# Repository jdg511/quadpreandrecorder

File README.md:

# Quad Preamp and Recorder

Compact four-channel ambisonic electret preamp, 192 kHz/24-bit recorder,
real-time binaural monitor, and touchscreen controller.

The hardware is derived from
[jdg511/Quadelectretpre](https://github.com/jdg511/Quadelectretpre) and is
redesigned as a mixed-signal two-layer PCB in a Hammond 1590XX enclosure.

## Project layout

- `hardware/` — KiCad project, fabrication package, design notes, and reviews.
- `tools/` — reproducible schematic, PCB, and fabrication-generation scripts.
- `firmware/` — recorder/DSP interface, pin map, file-naming rules, and
  implementation requirements. Production firmware is not included in Rev A.

## Revision status

The current design is **Rev C** (2026-09-08), routed for the compact
**Hammond 1590XX** (138 x 114 mm board, 145 x 121 x 39 mm enclosure). Rev C
takes the Rev B board and:

- adds a **USB-C** receptacle (J9) on the rear wall — 5 V power from any
  charger, power bank or computer port (TPS61175 boost + ADP7142 low-noise
  LDO make the 9 V analog rail), SD-card file transfer (MTP) and firmware
  updates; the 9 V barrel (J1) stays as an alternative input and moved to the
  rear-left wall;
- mutes the 1/4-inch line out with a signal relay (K1) while a computer is
  attached (ground-loop protection, on-screen warning with override);
- replaces the headphone pot with a **TPA6130A2** I2C-volume headphone amp
  (encoder / touchscreen control) and the pad toggle with a GPIO-driven
  level shifter (pad is a touchscreen control);
- changes the display to the LCDWiki **MSP3526** 3.5-inch IPS module with
  FT6336U **capacitive** touch (the MSP3520 named in Rev B is resistive).
- adds an internal **LiPo battery** (5000 mAh, 6-7 h) with a BQ24074 USB
  charger and a two-button soft-power gesture (hold RECORD + encoder push).

Walls: rear = SD slot + 9 V + USB-C, left = mic RJ45 (Amphenol RJHSE-5380),
right = headphones, front = line out; lid = display, record button, gain
encoder. Rev C3 (2026-09-12) removed the J6/J7 test headers (probe at
component pads or the TP3-TP14 pads), moved to a 4-layer SIG/GND/GND/SIG
stack, and made the mic input switchable from the screen: electret bias
off / 5 V / 9 V (one setting for all four channels) and, with the bias off,
the four RJ45 pairs become true balanced inputs for dynamic microphones
(two-op-amp instrumentation stage, +20.1 dB, SPICE-checked CMRR 58-67 dB
worst case across the audio band). The 9 V analog LDO is an ADP7142
(the TPS7A4701 it replaces had no distributor depth) and every BOM line
was re-checked for stock and price the same day. See
`hardware/reviews/audio-rules-check-revC3-fixes.md`, `hardware/mechanical.md`,
`hardware/connector-pinout.md` and `firmware/docs/REV-C-CONTROL-MODEL.md`.

ERC is clean and DRC (`--all-track-errors --schematic-parity
--severity-error`) reports 0 violations, 0 unconnected pads, 0 parity issues
on the routed board. The Gerbers, drills, BOM, placement CSVs, STEP and PDFs
in `hardware/manufacturing/` are regenerated from it
(`QuadPreRecorder-RevC-PCBWay-handoff.zip`). Rev B outputs are archived in
`hardware/manufacturing/revb-archive/`.

Still a human check before ordering: the physical Hammond 1590XX fit (wall
cutouts, button/shaft reach, the purchased MSP3526 module) — see
`hardware/enclosure-1590XX-desk-study.md` and
`hardware/reviews/rev-c-preorder-review.md`.

This is still new mixed-signal hardware, not a bench-proven production
revision. Read the prototype confirmations in `hardware/requirements.md` and
the order/bring-up notes in `hardware/manufacturing/README.md` before ordering.

## Rebuild

- `tools/route_pcb.ps1` regenerates the schematic/footprints/placement, runs
  Freerouting 1.9.0 (`tools/cache/freerouting19.jar`, single-threaded — the
  2.2.4 jar drops nets from its session export on this board), imports the
  route, adds the GND pours, and checks DRC. Allow ~35-60 minutes.
- `python tools/build_manufacturing.py` regenerates the complete PCBWay handoff
  with KiCad 10's command-line tools.

The checked-in routed board is the release artifact; rerouting is not required
to order it.

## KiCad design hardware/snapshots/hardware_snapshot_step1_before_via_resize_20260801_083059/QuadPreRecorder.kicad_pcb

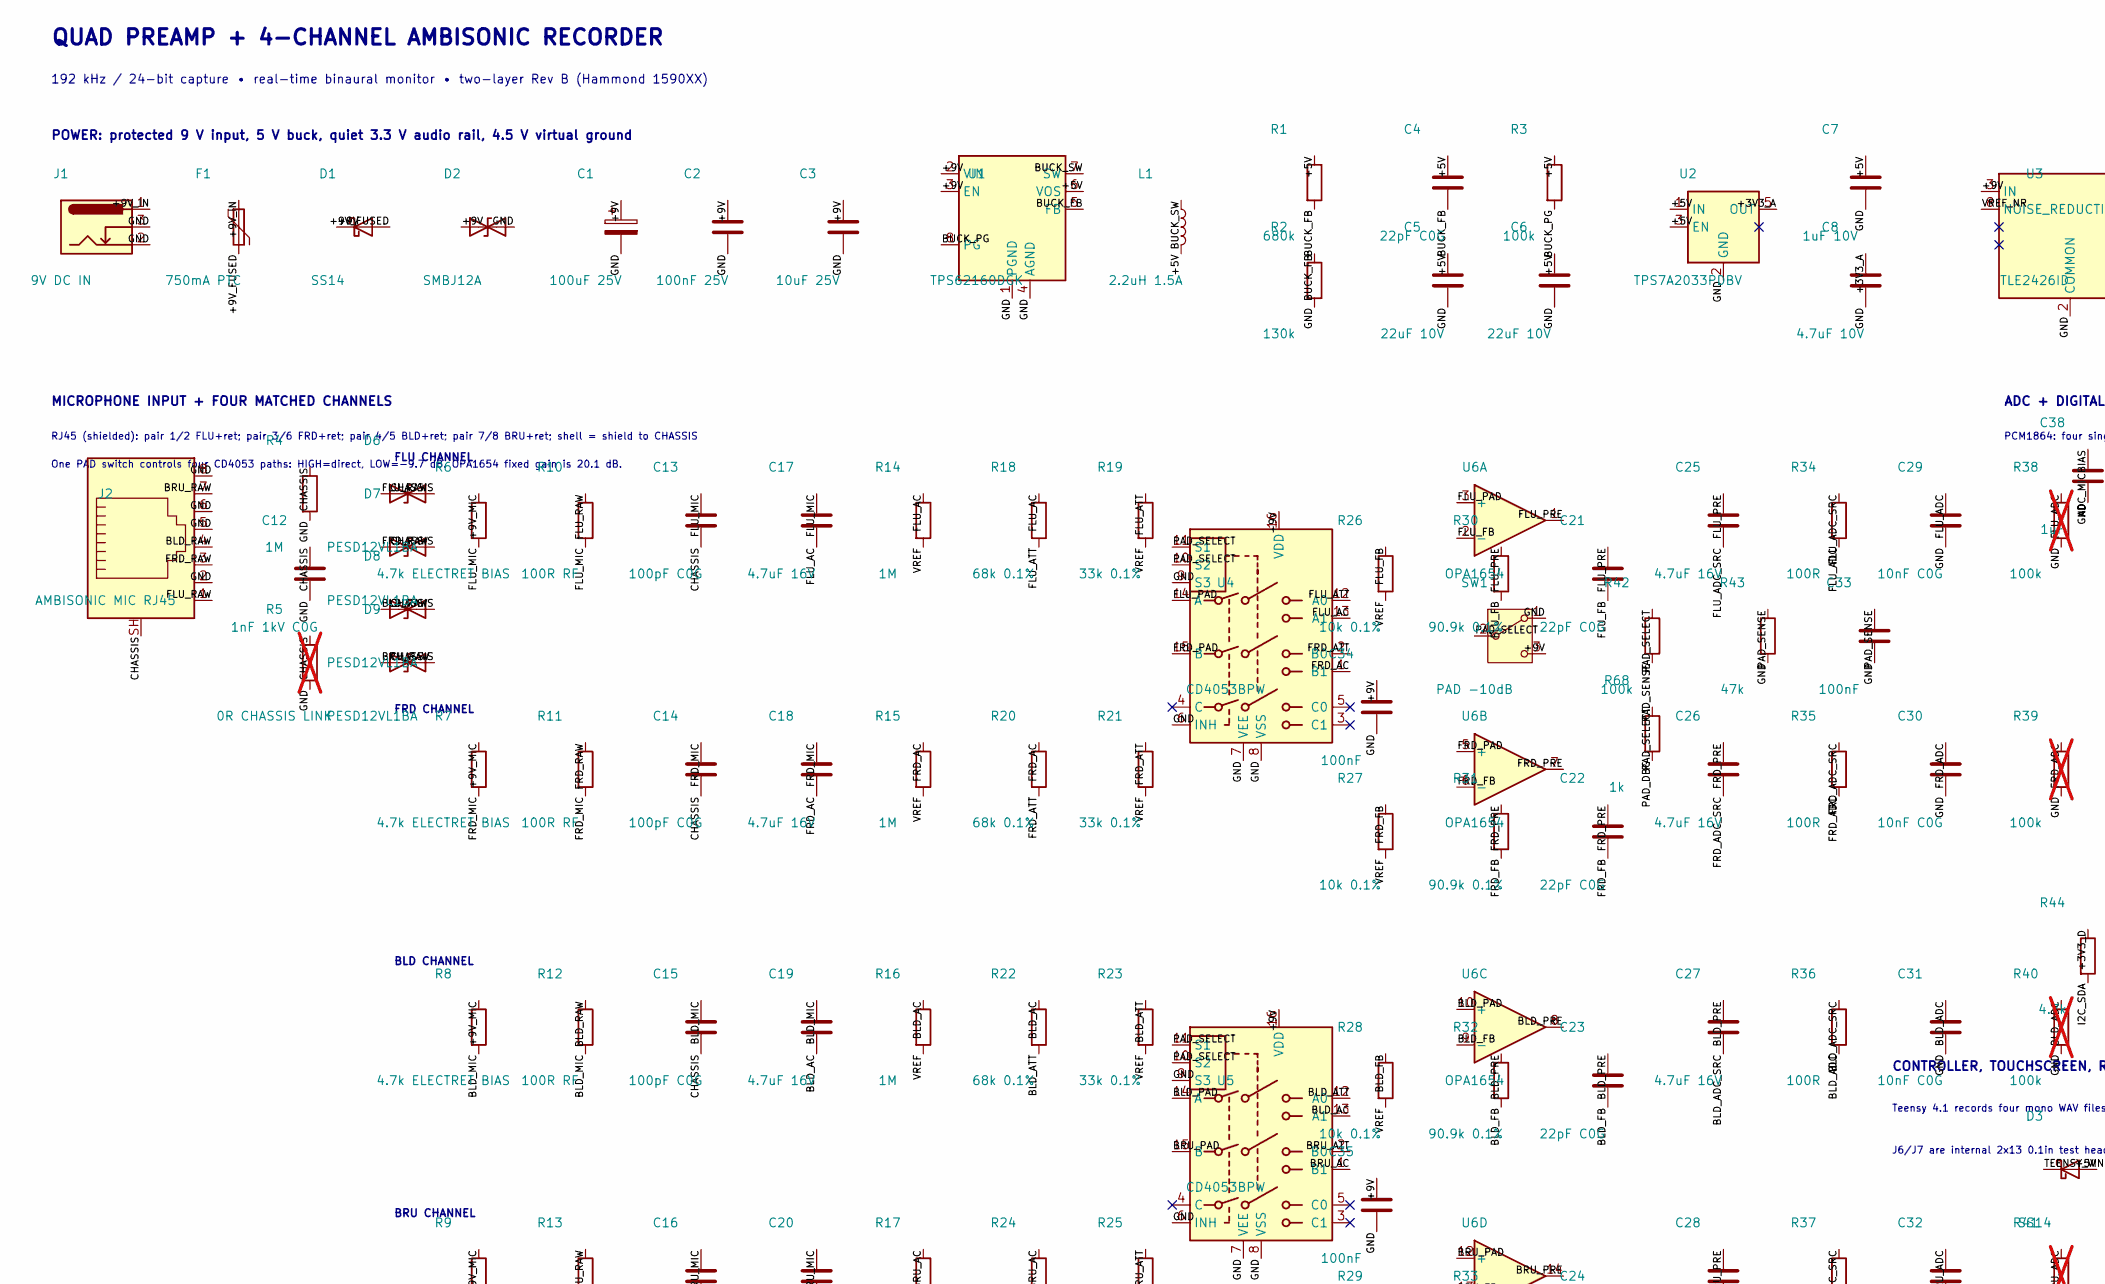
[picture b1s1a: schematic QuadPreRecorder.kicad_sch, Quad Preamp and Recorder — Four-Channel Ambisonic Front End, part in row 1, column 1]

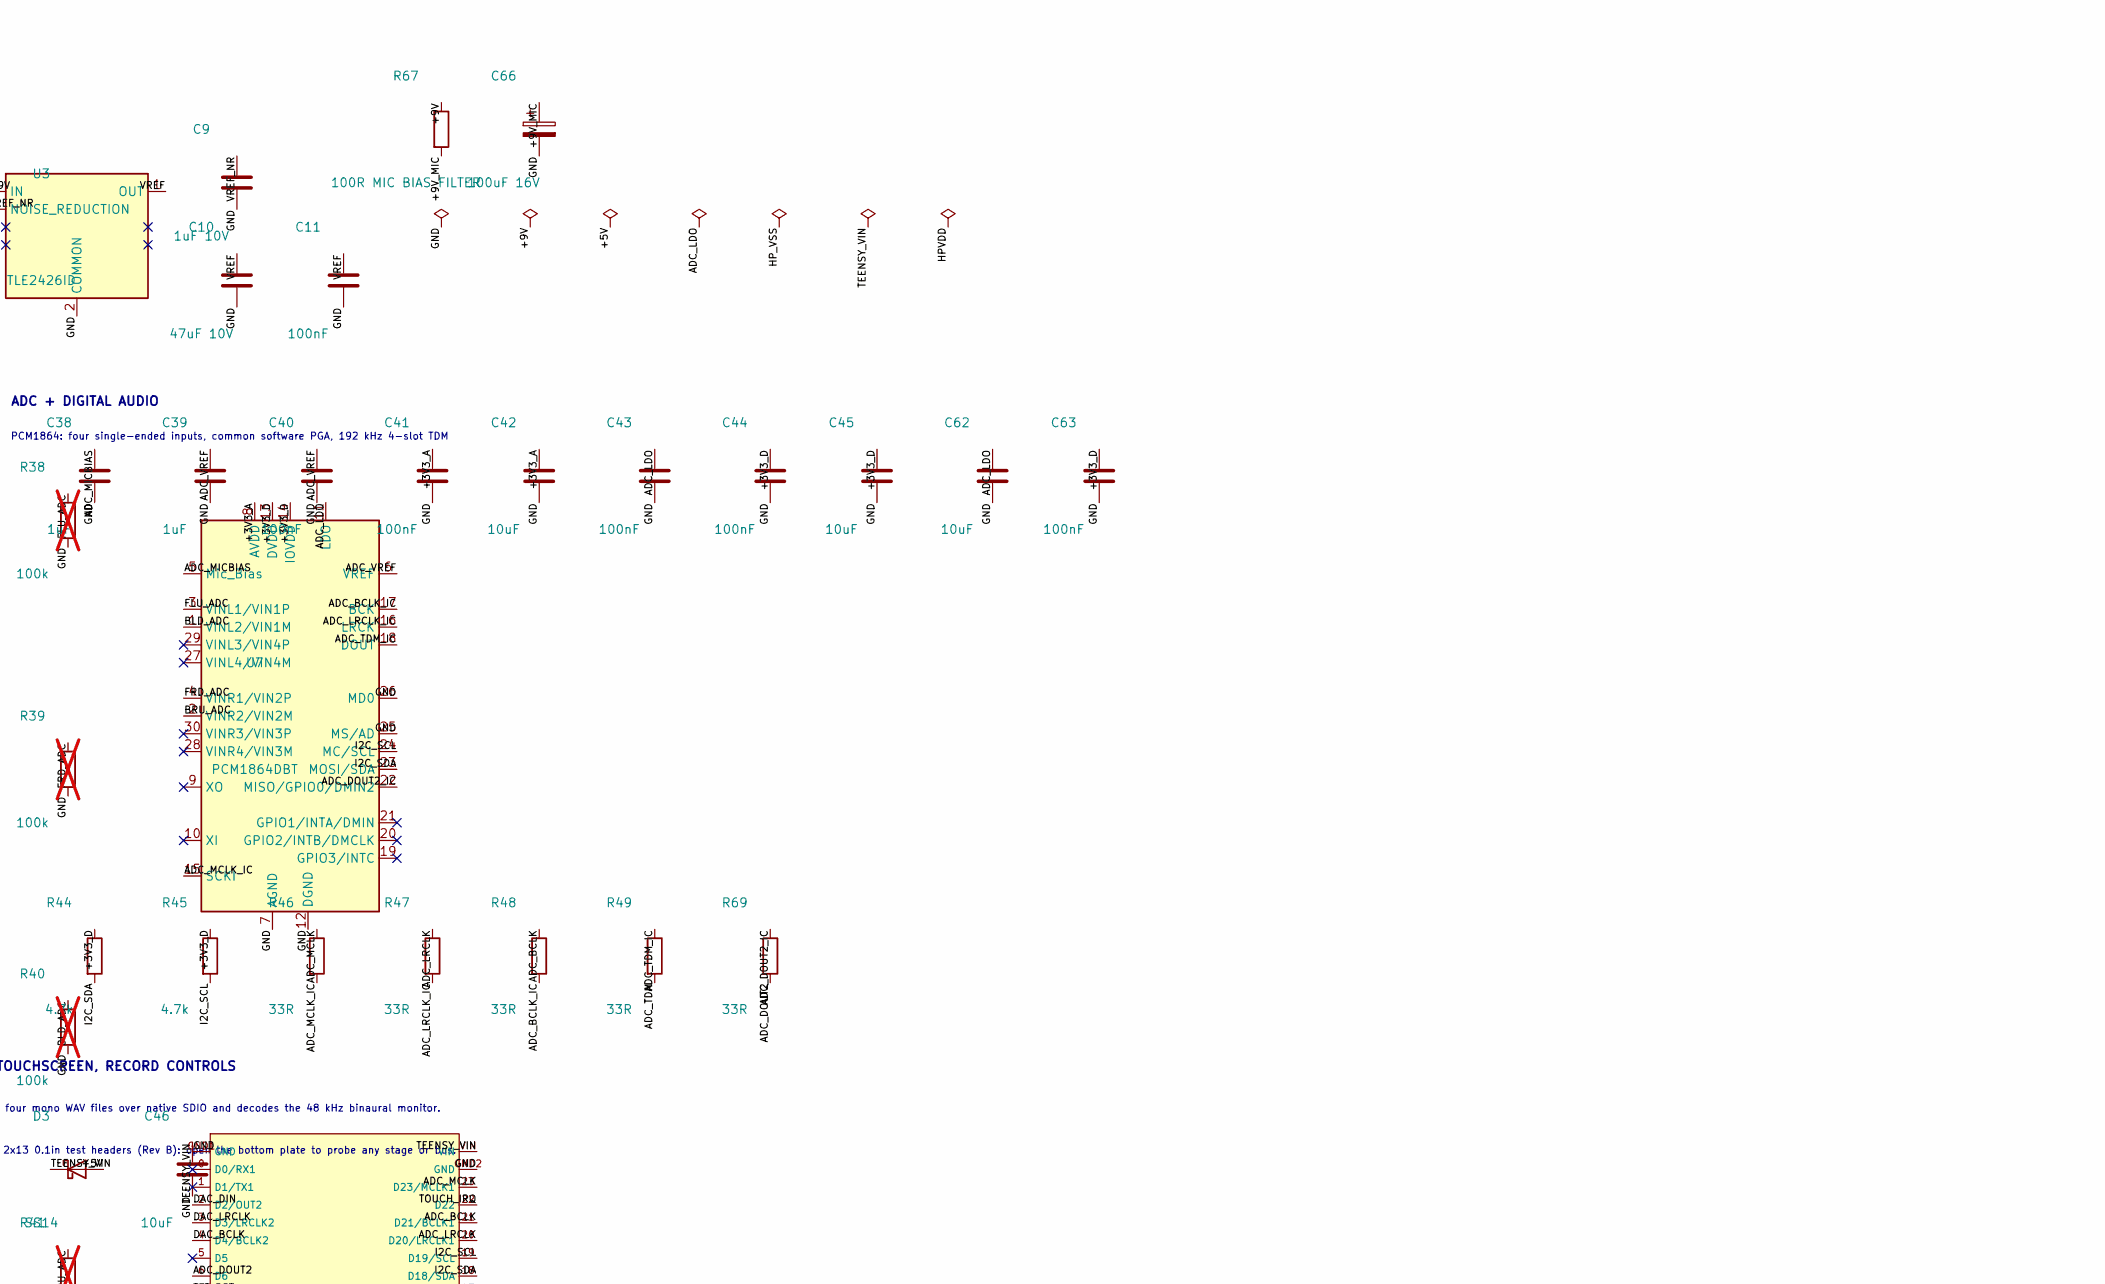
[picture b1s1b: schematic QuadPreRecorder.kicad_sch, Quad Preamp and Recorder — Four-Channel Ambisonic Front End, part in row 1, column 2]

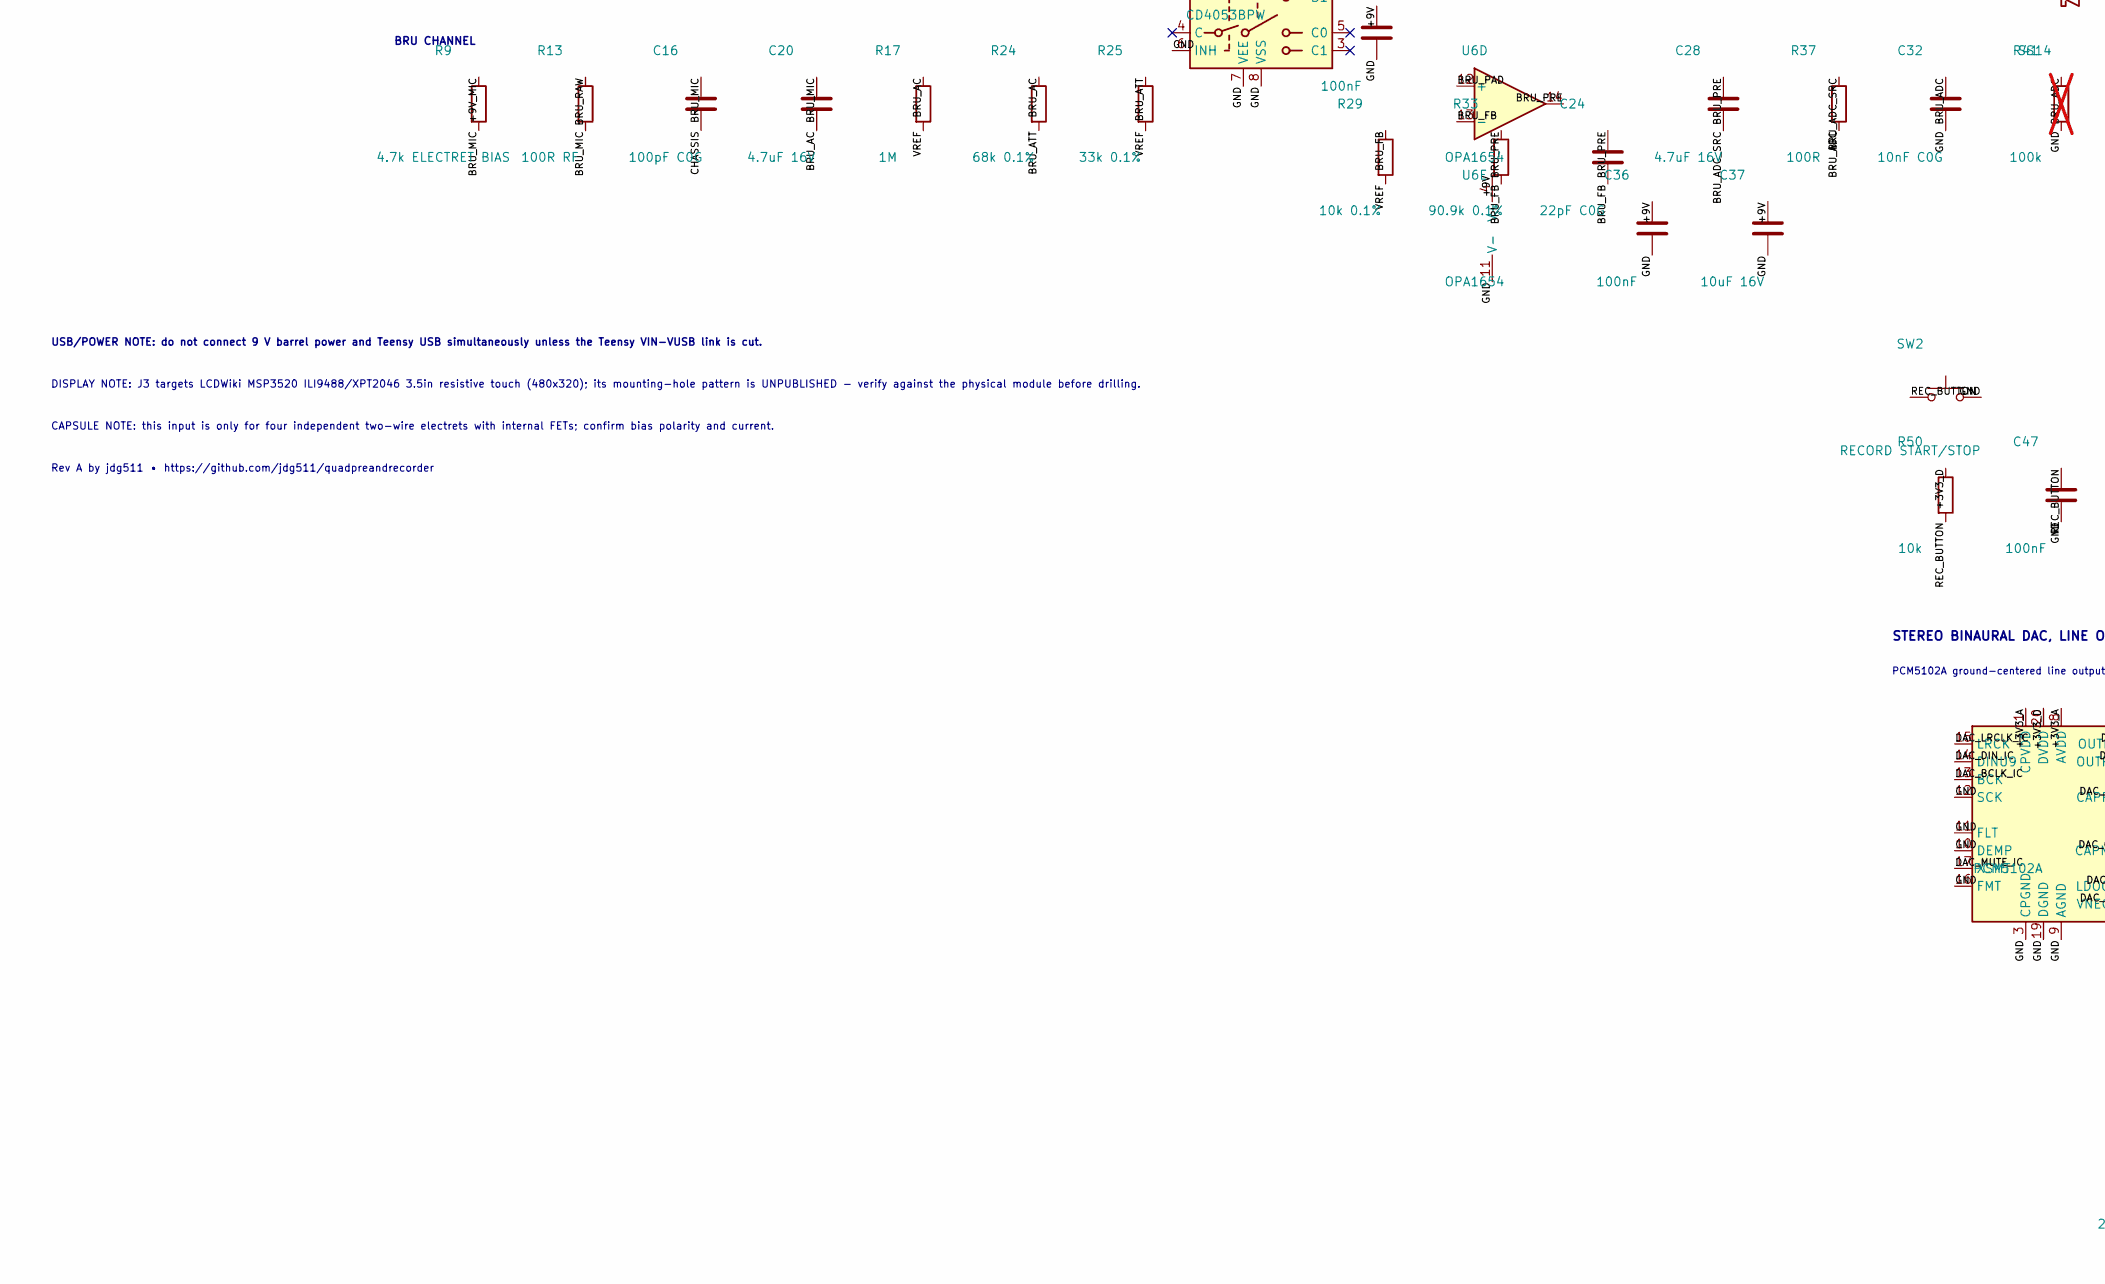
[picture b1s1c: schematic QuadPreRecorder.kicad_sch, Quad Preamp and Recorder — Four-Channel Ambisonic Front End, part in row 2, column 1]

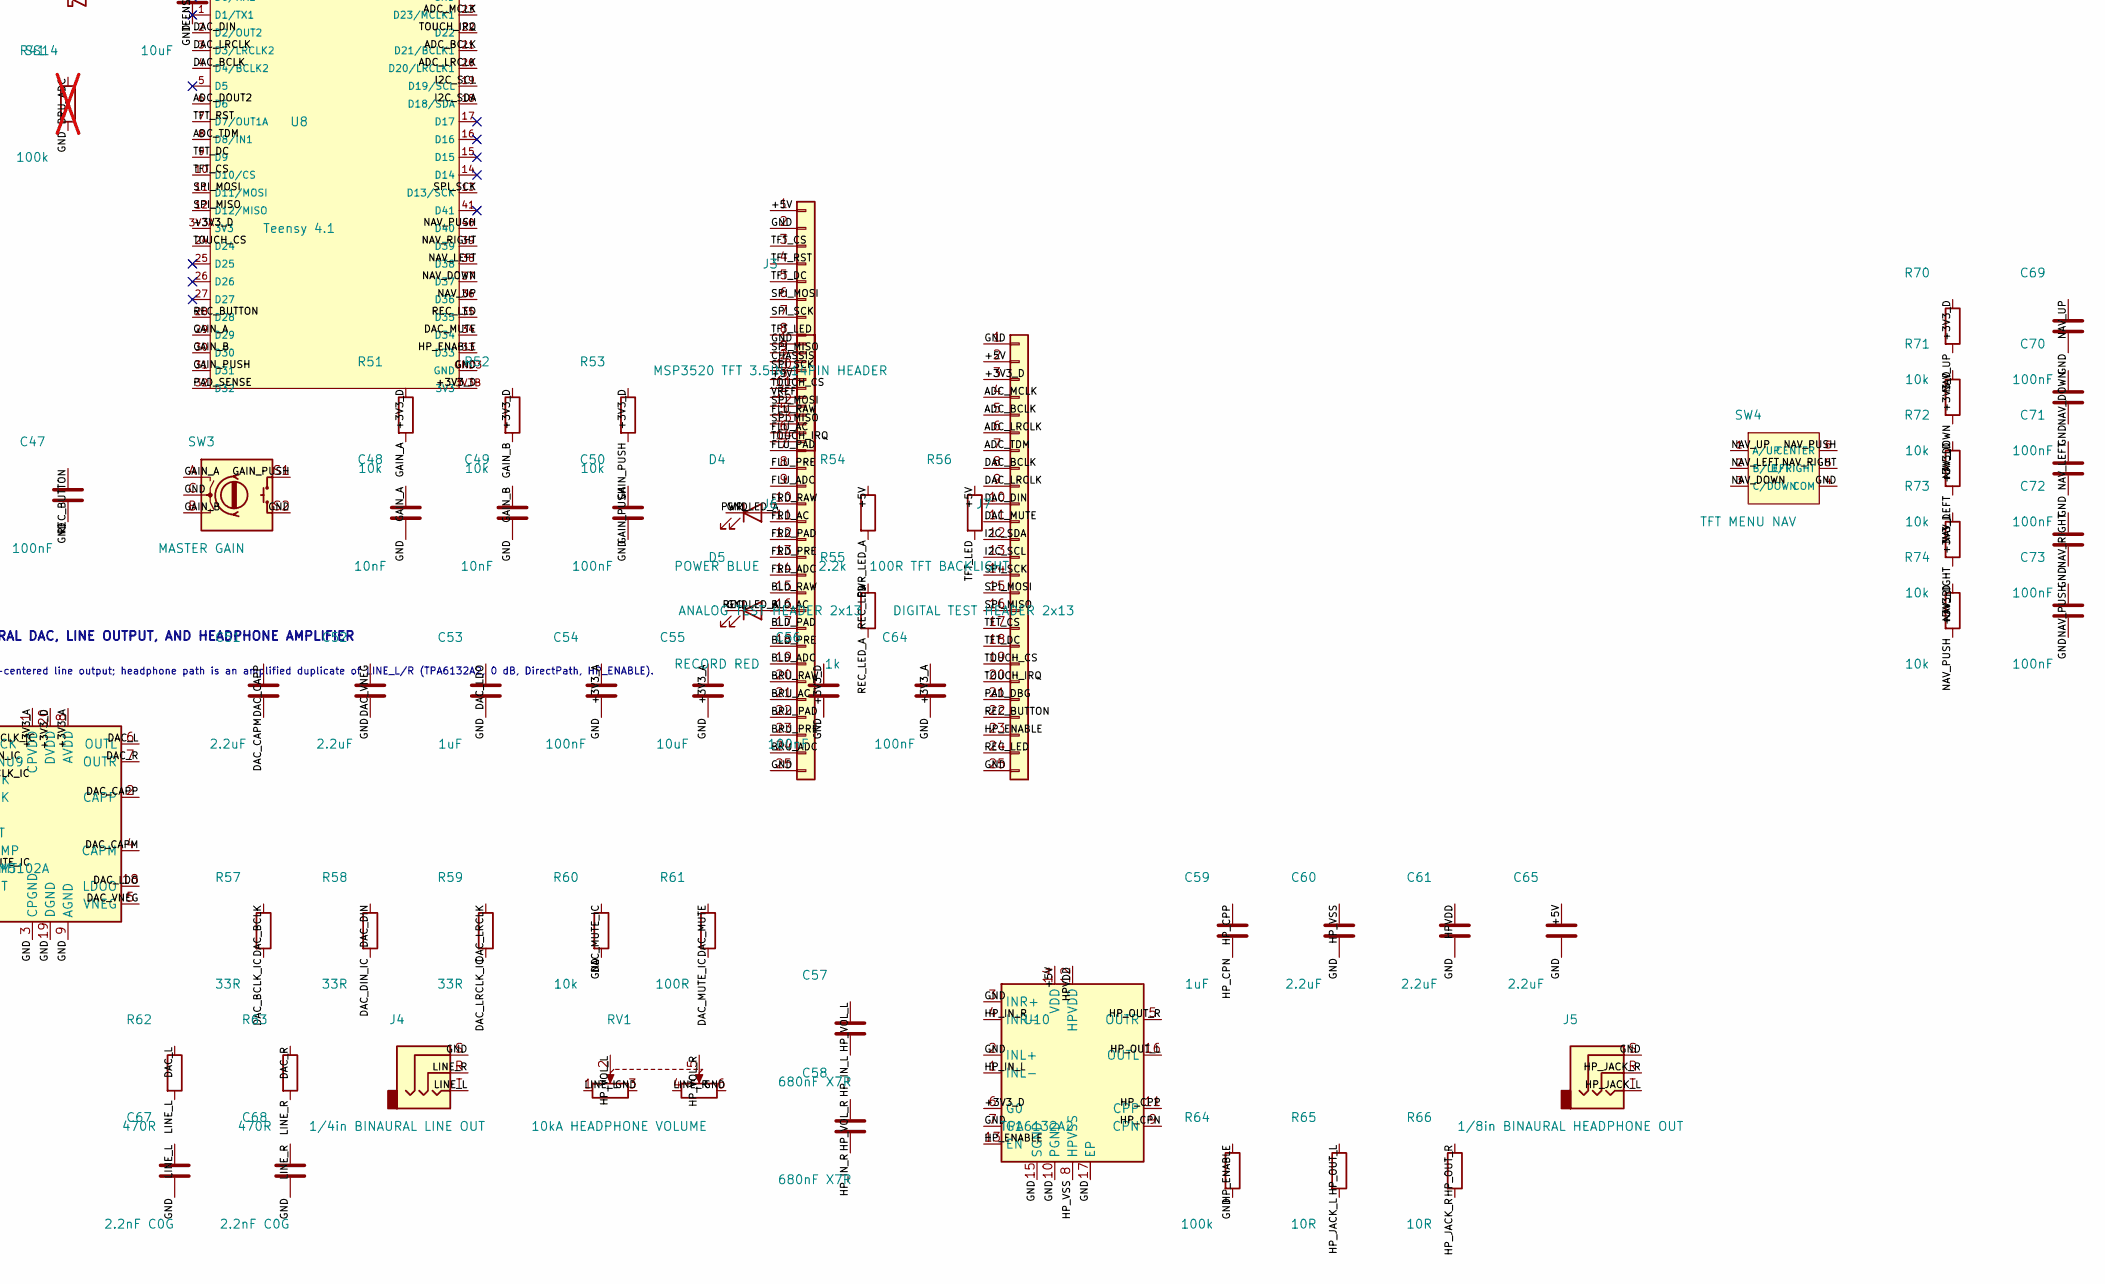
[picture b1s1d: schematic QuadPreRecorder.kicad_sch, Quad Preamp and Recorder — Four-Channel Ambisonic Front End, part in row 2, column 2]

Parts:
C1: 100uF 25V; CP_Elec_6.3x5.8; MPN EEE-FK series low-ESR aluminium electro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
C2: 100nF 25V; C_0805_2012Metric; MPN GRM series X7R/C0G
C3: 10uF 25V; C_1206_3216Metric; MPN GRM series X7R/C0G
C4, C21, C22, C23, C24: 22pF C0G; C_0603_1608Metric; MPN GRM series X7R/C0G
C5, C6: 22uF 10V; C_1206_3216Metric; MPN GRM series X7R/C0G
C7, C9: 1uF 10V; C_0805_2012Metric; MPN GRM series X7R/C0G
C8: 4.7uF 10V; C_0805_2012Metric; MPN GRM series X7R/C0G
C10: 47uF 10V; C_1206_3216Metric; MPN GRM series X7R/C0G
C11, C33, C34, C35, C36, C40, C41, C43, C44, C47, C50, C54, C56, C63, C64, C69, C70, C71, C72, C73: 100nF; C_0603_1608Metric; MPN GRM series X7R/C0G
C12: 1nF 1kV C0G; C_0805_2012Metric; MPN GRM series X7R/C0G
C13, C14, C15, C16: 100pF C0G; C_0603_1608Metric; MPN GRM series X7R/C0G
C17, C18, C19, C20, C25, C26, C27, C28: 4.7uF 16V; C_1206_3216Metric; MPN GRM series X7R/C0G
C29, C30, C31, C32: 10nF C0G; C_0603_1608Metric; MPN GRM series X7R/C0G
C37: 10uF 16V; C_1206_3216Metric; MPN GRM series X7R/C0G
C38, C39, C53: 1uF; C_0805_2012Metric; MPN GRM series X7R/C0G
C42, C45, C46, C55, C62: 10uF; C_1206_3216Metric; MPN GRM series X7R/C0G
C48, C49: 10nF; C_0603_1608Metric; MPN GRM series X7R/C0G
C51, C52: 2.2uF; C_0805_2012Metric; MPN GRM series X7R/C0G
C57: 680nF X7R; C_0805_2012Metric; MPN GRM series X7R/C0G
C58: 680nF X7R; C_0603_1608Metric; MPN GRM series X7R/C0G
C59: 1uF; C_0603_1608Metric; MPN GRM series X7R/C0G
C60, C61, C65: 2.2uF; C_0603_1608Metric; MPN GRM series X7R/C0G
C66: 100uF 16V; CP_Elec_6.3x5.8; MPN EEE-FK series low-ESR aluminium electro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
C67, C68: 2.2nF C0G; C_0603_1608Metric; MPN GRM series X7R/C0G
D1, D3: SS14; D_SMA; MPN SS14-13-F
D2: SMBJ12A; D_SMB; MPN SMBJ12A
D4: POWER BLUE; LED_0603_1608Metric; MPN LTST-C190TBKT
D5: RECORD RED; LED_0603_1608Metric; MPN LTST-C190KRKT
D6, D7, D8, D9: PESD12VL1BA; D_SOD-323; MPN PESD12VL1BA,115
F1: 750mA PTC; Fuse_1206_3216Metric; MPN 1206L075/13.2WR
J1: 9V DC IN; BarrelJack_CUI_PJ-102AH_Horizontal; MPN PJ-102AH
J2: AMBISONIC MIC RJ45; RJ45_Amphenol_RJHSE5380; MPN RJHSE-5380
J3: MSP3520 TFT 3.5IN 14PIN HEADER; PinHeader_1x14_P2.54mm_Vertical; MPN PRPC014SAAN-RC
J4: 1/4in BINAURAL LINE OUT; Jack_6.35mm_Neutrik_NRJ6HF_Horizontal; MPN NRJ6HF
J5: 1/8in BINAURAL HEADPHONE OUT; Jack_3.5mm_CUI_SJ1-3533NG_Horizontal; MPN SJ1-3533NG
J6: ANALOG TEST HEADER 2x13; PinHeader_2x13_P2.54mm_Vertical; MPN 2x13 0.1in pin header
J7: DIGITAL TEST HEADER 2x13; PinHeader_2x13_P2.54mm_Vertical; MPN 2x13 0.1in pin header
L1: 2.2uH 1.5A; L_Abracon_ASPIAIG-F4020; MPN ASPIAIG-F4020-2R2M-T
R1: 680k; R_0603_1608Metric; MPN RC0603FR series, 1%
R2: 130k; R_0603_1608Metric; MPN RC0603FR series, 1%
R3, R42, R64: 100k; R_0603_1608Metric; MPN RC0603FR series, 1%
R4, R14, R15, R16, R17: 1M; R_0603_1608Metric; MPN RC0603FR series, 1%
R5: 0R CHASSIS LINK; R_0603_1608Metric; MPN RC0603FR series, 1%; not fitted
R6, R7, R8, R9: 4.7k ELECTRET BIAS; R_0603_1608Metric; MPN RC0603FR series, 1%
R10, R11, R12, R13: 100R RF; R_0603_1608Metric; MPN RC0603FR series, 1%
R18, R20, R22, R24: 68k 0.1%; R_0603_1608Metric; MPN TNPW0603 series, 0.1%
R19, R21, R23, R25: 33k 0.1%; R_0603_1608Metric; MPN TNPW0603 series, 0.1%
R26, R27, R28, R29: 10k 0.1%; R_0603_1608Metric; MPN TNPW0603 series, 0.1%
R30, R31, R32, R33: 90.9k 0.1%; R_0603_1608Metric; MPN TNPW0603 series, 0.1%
R34, R35, R36, R37, R61: 100R; R_0603_1608Metric; MPN RC0603FR series, 1%
R38, R39, R40, R41: 100k; R_0603_1608Metric; MPN RC0603FR series, 1%; not fitted
R43: 47k; R_0603_1608Metric; MPN RC0603FR series, 1%
R44, R45: 4.7k; R_0603_1608Metric; MPN RC0603FR series, 1%
R46, R47, R48, R49, R57, R58, R59, R69: 33R; R_0603_1608Metric; MPN RC0603FR series, 1%
R50, R51, R52, R53, R60, R70, R71, R72, R73, R74: 10k; R_0603_1608Metric; MPN RC0603FR series, 1%
R54: 2.2k; R_0603_1608Metric; MPN RC0603FR series, 1%
R55, R68: 1k; R_0603_1608Metric; MPN RC0603FR series, 1%
R56: 100R TFT BACKLIGHT; R_0805_2012Metric; MPN RC0805FR-07100RL
R62, R63: 470R; R_0603_1608Metric; MPN RC0603FR series, 1%
R65, R66: 10R; R_0603_1608Metric; MPN RC0603FR series, 1%
R67: 100R MIC BIAS FILTER; R_0603_1608Metric; MPN RC0603FR series, 1%
RV1: 10kA HEADPHONE VOLUME; RK097_Dual_Horizontal_NoEdgeGuide; MPN RK0971221-F15-C0-A103
SW1: PAD -10dB; SW_Toggle_ESwitch_100SP_M7; MPN 100SP1T1B1M7REH
SW2: RECORD START/STOP; SW_PUSH-12mm; MPN B3F-5150
SW3: MASTER GAIN; RotaryEncoder_Alps_EC11E-Switch_Vertical_H20mm; MPN EC11E15244G1
SW4: TFT MENU NAV; SW_Nav_ALPS_SKQUCAA010; MPN SKQUCAA010
U1: TPS62160DGK; VSSOP-8_3x3mm_P0.65mm; MPN TPS62160DGKR
U2: TPS7A2033PDBV; SOT-23-5; MPN TPS7A2033PDBVR
U3: TLE2426ID; SOIC-8_3.9x4.9mm_P1.27mm; MPN TLE2426IDR
U4, U5: CD4053BPW; TSSOP-16_4.4x5mm_P0.65mm; MPN CD4053BPWR
U6: OPA1654; TSSOP-14_4.4x5mm_P0.65mm; MPN OPA1654AIPWR
U7: PCM1864DBT; TSSOP-30_4.4x7.8mm_P0.5mm; MPN PCM1864DBTR
U8: Teensy 4.1; Teensy41_Socket; MPN TEENSY41
U9: PCM5102A; TSSOP-20_4.4x6.5mm_P0.65mm; MPN PCM5102APWR
U10: TPA6132A2; WQFN-16-1EP_3x3mm_P0.5mm_EP1.6x1.6mm; MPN TPA6132A2RTER

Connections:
+3V3_A: C8.1, C41.1, C42.1, C54.1, C55.1, C64.1, U2.5 (OUT), U7.8 (AVDD), U9.1 (CPVDD), U9.8 (AVDD)
+3V3_D: C44.1, C45.1, C56.1, C63.1, J7.3, R44.1, R45.1, R50.1, R51.1, R52.1, R53.1, R70.1, R71.1, R72.1, R73.1, R74.1, U7.13 (DVDD), U7.14 (IOVDD), U8.3V3A (3V3), U8.3V3B (3V3), U9.20 (DVDD), U10.6 (G0)
+5V: C4.1, C5.1, C6.1, C7.1, C65.1, D3.2 (A), J3.1, J7.2, L1.2, R1.1, R3.1, R54.1, R56.1, U1.6 (VOS), U2.1 (IN), U2.3 (EN), U10.14 (VDD)
+9V: C1.1, C2.1, C3.1, C34.1, C35.1, C36.1, C37.1, D1.1 (K), D2.1 (A1), J6.3, R67.1, SW1.3 (C), U1.2 (VIN), U1.3 (EN), U3.3 (IN), U4.16 (VDD), U5.16 (VDD), U6.4 (V+)
+9V_FUSED: D1.2 (A), F1.2
+9V_IN: F1.1, J1.1
+9V_MIC: C66.1, R6.1, R7.1, R8.1, R9.1, R67.2
ADC_BCLK: J7.5, R48.1, U8.21 (D21/BCLK1)
ADC_BCLK_IC: R48.2, U7.17 (BCK)
ADC_DOUT2: R69.2, U8.6 (D6)
ADC_DOUT2_IC: R69.1, U7.22 (MISO/GPIO0/DMIN2)
ADC_LDO: C43.1, C62.1, U7.11 (LDO)
ADC_LRCLK: J7.6, R47.1, U8.20 (D20/LRCLK1)
ADC_LRCLK_IC: R47.2, U7.16 (LRCK)
ADC_MCLK: J7.4, R46.1, U8.23 (D23/MCLK1)
ADC_MCLK_IC: R46.2, U7.15 (SCKI)
ADC_MICBIAS: C38.1, U7.5 (Mic_Bias)
ADC_TDM: J7.7, R49.2, U8.8 (D8/IN1)
ADC_TDM_IC: R49.1, U7.18 (DOUT)
ADC_VREF: C39.1, C40.1, U7.6 (VREF)
BLD_AC: C19.2, J6.16, R16.1, R22.1, U5.13 (A1)
BLD_ADC: C31.1, J6.19, R36.2, R40.1, U7.1 (VINL2/VIN1M)
BLD_ADC_SRC: C27.2, R36.1
BLD_ATT: R22.2, R23.1, U5.12 (A0)
BLD_FB: C23.2, R28.1, R32.2, U6.9 (-)
BLD_MIC: C15.1, C19.1, R8.2, R12.2
BLD_PAD: J6.17, U5.14 (A), U6.10 (+)
BLD_PRE: C23.1, C27.1, J6.18, R32.1, U6.8
BLD_RAW: D8.1 (A1), J2.4, J6.15, R12.1
BRU_AC: C20.2, J6.21, R17.1, R24.1, U5.1 (B1)
BRU_ADC: C32.1, J6.24, R37.2, R41.1, U7.2 (VINR2/VIN2M)
BRU_ADC_SRC: C28.2, R37.1
BRU_ATT: R24.2, R25.1, U5.2 (B0)
BRU_FB: C24.2, R29.1, R33.2, U6.13 (-)
BRU_MIC: C16.1, C20.1, R9.2, R13.2
BRU_PAD: J6.22, U5.15 (B), U6.12 (+)
BRU_PRE: C24.1, C28.1, J6.23, R33.1, U6.14
BRU_RAW: D9.1 (A1), J2.7, J6.20, R13.1
BUCK_FB: C4.2, R1.2, R2.1, U1.5 (FB)
BUCK_PG: R3.2, U1.8 (PG)
BUCK_SW: L1.1, U1.7 (SW)
CHASSIS: C12.1, C13.2, C14.2, C15.2, C16.2, D6.2 (A2), D7.2 (A2), D8.2 (A2), D9.2 (A2), J2.SH, J6.2, R4.1, R5.1
DAC_BCLK: J7.8, R57.1, U8.4 (D4/BCLK2)
DAC_BCLK_IC: R57.2, U9.13 (BCK)
DAC_CAPM: C51.2, U9.4 (CAPM)
DAC_CAPP: C51.1, U9.2 (CAPP)
DAC_DIN: J7.10, R58.1, U8.2 (D2/OUT2)
DAC_DIN_IC: R58.2, U9.14 (DIN)
DAC_L: R62.1, U9.6 (OUTL)
DAC_LDO: C53.1, U9.18 (LDOO)
DAC_LRCLK: J7.9, R59.1, U8.3 (D3/LRCLK2)
DAC_LRCLK_IC: R59.2, U9.15 (LRCK)
DAC_MUTE: J7.11, R61.1, U8.34 (D34)
DAC_MUTE_IC: R60.1, R61.2, U9.17 (XSMT)
DAC_R: R63.1, U9.7 (OUTR)
DAC_VNEG: C52.1, U9.5 (VNEG)
FLU_AC: C17.2, J6.6, R14.1, R18.1, U4.13 (A1)
FLU_ADC: C29.1, J6.9, R34.2, R38.1, U7.3 (VINL1/VIN1P)
FLU_ADC_SRC: C25.2, R34.1
FLU_ATT: R18.2, R19.1, U4.12 (A0)
FLU_FB: C21.2, R26.1, R30.2, U6.2 (-)
FLU_MIC: C13.1, C17.1, R6.2, R10.2
FLU_PAD: J6.7, U4.14 (A), U6.3 (+)
FLU_PRE: C21.1, C25.1, J6.8, R30.1, U6.1
FLU_RAW: D6.1 (A1), J2.1, J6.5, R10.1
FRD_AC: C18.2, J6.11, R15.1, R20.1, U4.1 (B1)
FRD_ADC: C30.1, J6.14, R35.2, R39.1, U7.4 (VINR1/VIN2P)
FRD_ADC_SRC: C26.2, R35.1
FRD_ATT: R20.2, R21.1, U4.2 (B0)
FRD_FB: C22.2, R27.1, R31.2, U6.6 (-)
FRD_MIC: C14.1, C18.1, R7.2, R11.2
FRD_PAD: J6.12, U4.15 (B), U6.5 (+)
FRD_PRE: C22.1, C26.1, J6.13, R31.1, U6.7
FRD_RAW: D7.1 (A1), J2.3, J6.10, R11.1
GAIN_A: C48.1, R51.2, SW3.A, U8.29 (D29)
GAIN_B: C49.1, R52.2, SW3.B, U8.30 (D30)
GAIN_PUSH: C50.1, R53.2, SW3.S1, U8.31 (D31)
GND: C1.2, C2.2, C3.2, C5.2, C6.2, C7.2, C8.2, C9.2, C10.2, C11.2, C12.2, C29.2, C30.2, C31.2, C32.2, C33.2, C34.2, C35.2, C36.2, C37.2, C38.2, C39.2, C40.2, C41.2, C42.2, C43.2, C44.2, C45.2, C46.2, C47.2, C48.2, C49.2, C50.2, C52.2, C53.2, C54.2, C55.2, C56.2, C60.2, C61.2, C62.2, C63.2, C64.2, C65.2, C66.2, C67.2, C68.2, C69.2, C70.2, C71.2, C72.2, C73.2, D2.2 (A2), D4.1 (K), D5.1 (K), J1.2, J1.3, J2.2, J2.5, J2.6, J2.8, J3.2, J4.S, J5.S, J6.1, J6.25, J7.1, J7.25, R2.2, R4.2, R5.2, R38.2, R39.2, R40.2, R41.2, R43.2, R60.2, R64.2, RV1.3, RV1.6, SW1.1 (A), SW2.2, SW3.C, SW3.S2, SW4.4 (COM), U1.1 (PGND), U1.4 (AGND), U2.2 (GND), U3.2 (COMMON), U4.6 (INH), U4.7 (VEE), U4.8 (VSS), U4.9 (S3), U5.6 (INH), U5.7 (VEE), U5.8 (VSS), U5.9 (S3), U6.11 (V-), U7.7 (AGND), U7.12 (DGND), U7.25 (MS/AD), U7.26 (MD0), U8.GND1 (GND), U8.GND2 (GND), U8.GND3 (GND), U9.3 (CPGND), U9.9 (AGND), U9.10 (DEMP), U9.11 (FLT), U9.12 (SCK), U9.16 (FMT), U9.19 (DGND), U10.2 (INL+), U10.3 (INR+), U10.7 (G1), U10.10 (PGND), U10.15 (SGND), U10.17 (EP)
HPVDD: C61.1, U10.12 (HPVDD)
HP_CPN: C59.2, U10.9 (CPN)
HP_CPP: C59.1, U10.11 (CPP)
HP_ENABLE: J7.23, R64.1, U8.33 (D33), U10.13 (EN)
HP_IN_L: C57.2, U10.1 (INL-)
HP_IN_R: C58.2, U10.4 (INR-)
HP_JACK_L: J5.T, R65.2
HP_JACK_R: J5.R, R66.2
HP_OUT_L: R65.1, U10.16 (OUTL)
HP_OUT_R: R66.1, U10.5 (OUTR)
HP_VOL_L: C57.1, RV1.2
HP_VOL_R: C58.1, RV1.5
HP_VSS: C60.1, U10.8 (HPVSS)
I2C_SCL: J7.13, R45.2, U7.24 (MC/SCL), U8.19 (D19/SCL)
I2C_SDA: J7.12, R44.2, U7.23 (MOSI/SDA), U8.18 (D18/SDA)
LINE_L: C67.1, J4.T, R62.2, RV1.1
LINE_R: C68.1, J4.R, R63.2, RV1.4
NAV_DOWN: C70.1, R71.2, SW4.3 (C/DOWN), U8.37 (D37)
NAV_LEFT: C71.1, R72.2, SW4.2 (B/LEFT), U8.38 (D38)
NAV_PUSH: C73.1, R74.2, SW4.6 (CENTER), U8.40 (D40)
NAV_RIGHT: C72.1, R73.2, SW4.5 (D/RIGHT), U8.39 (D39)
NAV_UP: C69.1, R70.2, SW4.1 (A/UP), U8.36 (D36)
PAD_DBG: J7.21, R68.2
PAD_SELECT: R42.1, R68.1, SW1.2 (B), U4.10 (S2), U4.11 (S1), U5.10 (S2), U5.11 (S1)
PAD_SENSE: C33.1, R42.2, R43.1, U8.32 (D32)
PWR_LED_A: D4.2 (A), R54.2
REC_BUTTON: C47.1, J7.22, R50.2, SW2.1, U8.28 (D28)
REC_LED: J7.24, R55.1, U8.35 (D35)
REC_LED_A: D5.2 (A), R55.2
SPI_MISO: J3.9, J3.13, J7.16, U8.12 (D12/MISO)
SPI_MOSI: J3.6, J3.12, J7.15, U8.11 (D11/MOSI)
SPI_SCK: J3.7, J3.10, J7.14, U8.13 (D13/SCK)
TEENSY_VIN: C46.1, D3.1 (K), U8.VIN
TFT_CS: J3.3, J7.17, U8.10 (D10/CS)
TFT_DC: J3.5, J7.18, U8.9 (D9)
TFT_LED: J3.8, R56.2
TFT_RST: J3.4, U8.7 (D7/OUT1A)
TOUCH_CS: J3.11, J7.19, U8.24 (D24)
TOUCH_IRQ: J3.14, J7.20, U8.22 (D22)
VREF: C10.1, C11.1, J6.4, R14.2, R15.2, R16.2, R17.2, R19.2, R21.2, R23.2, R25.2, R26.2, R27.2, R28.2, R29.2, U3.1 (OUT)
VREF_NR: C9.1, U3.8 (NOISE_REDUCTION)

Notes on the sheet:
QUAD PREAMP + 4-CHANNEL AMBISONIC RECORDER
192 kHz / 24-bit capture • real-time binaural monitor • two-layer Rev B (Hammond 1590XX)
POWER: protected 9 V input, 5 V buck, quiet 3.3 V audio rail, 4.5 V virtual ground
MICROPHONE INPUT + FOUR MATCHED CHANNELS
RJ45 (shielded): pair 1/2 FLU+ret; pair 3/6 FRD+ret; pair 4/5 BLD+ret; pair 7/8 BRU+ret; shell = shield to CHASSIS
One PAD switch controls four CD4053 paths: HIGH=direct, LOW=-9.7 dB. OPA1654 fixed gain is 20.1 dB.
FLU CHANNEL
FRD CHANNEL
BLD CHANNEL
BRU CHANNEL
ADC + DIGITAL AUDIO
PCM1864: four single-ended inputs, common software PGA, 192 kHz 4-slot TDM
CONTROLLER, TOUCHSCREEN, RECORD CONTROLS
Teensy 4.1 records four mono WAV files over native SDIO and decodes the 48 kHz binaural monitor.
J6/J7 are internal 2x13 0.1in test headers (Rev B): open the bottom plate to probe any stage or bus.
STEREO BINAURAL DAC, LINE OUTPUT, AND HEADPHONE AMPLIFIER
PCM5102A ground-centered line output; headphone path is an amplified duplicate of LINE_L/R (TPA6132A2, 0 dB, DirectPath, HP_ENABLE).
USB/POWER NOTE: do not connect 9 V barrel power and Teensy USB simultaneously unless the Teensy VIN-VUSB link is cut.
DISPLAY NOTE: J3 targets LCDWiki MSP3520 ILI9488/XPT2046 3.5in resistive touch (480x320); its mounting-hole pattern is UNPUBLISHED - verify against the physical module before drilling.
CAPSULE NOTE: this input is only for four independent two-wire electrets with internal FETs; confirm bias polarity and current.
Rev A by jdg511 • https://github.com/jdg511/quadpreandrecorder
